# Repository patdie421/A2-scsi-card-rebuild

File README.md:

Apple II SCSI card rebuild

Work in progress, not yet tested.

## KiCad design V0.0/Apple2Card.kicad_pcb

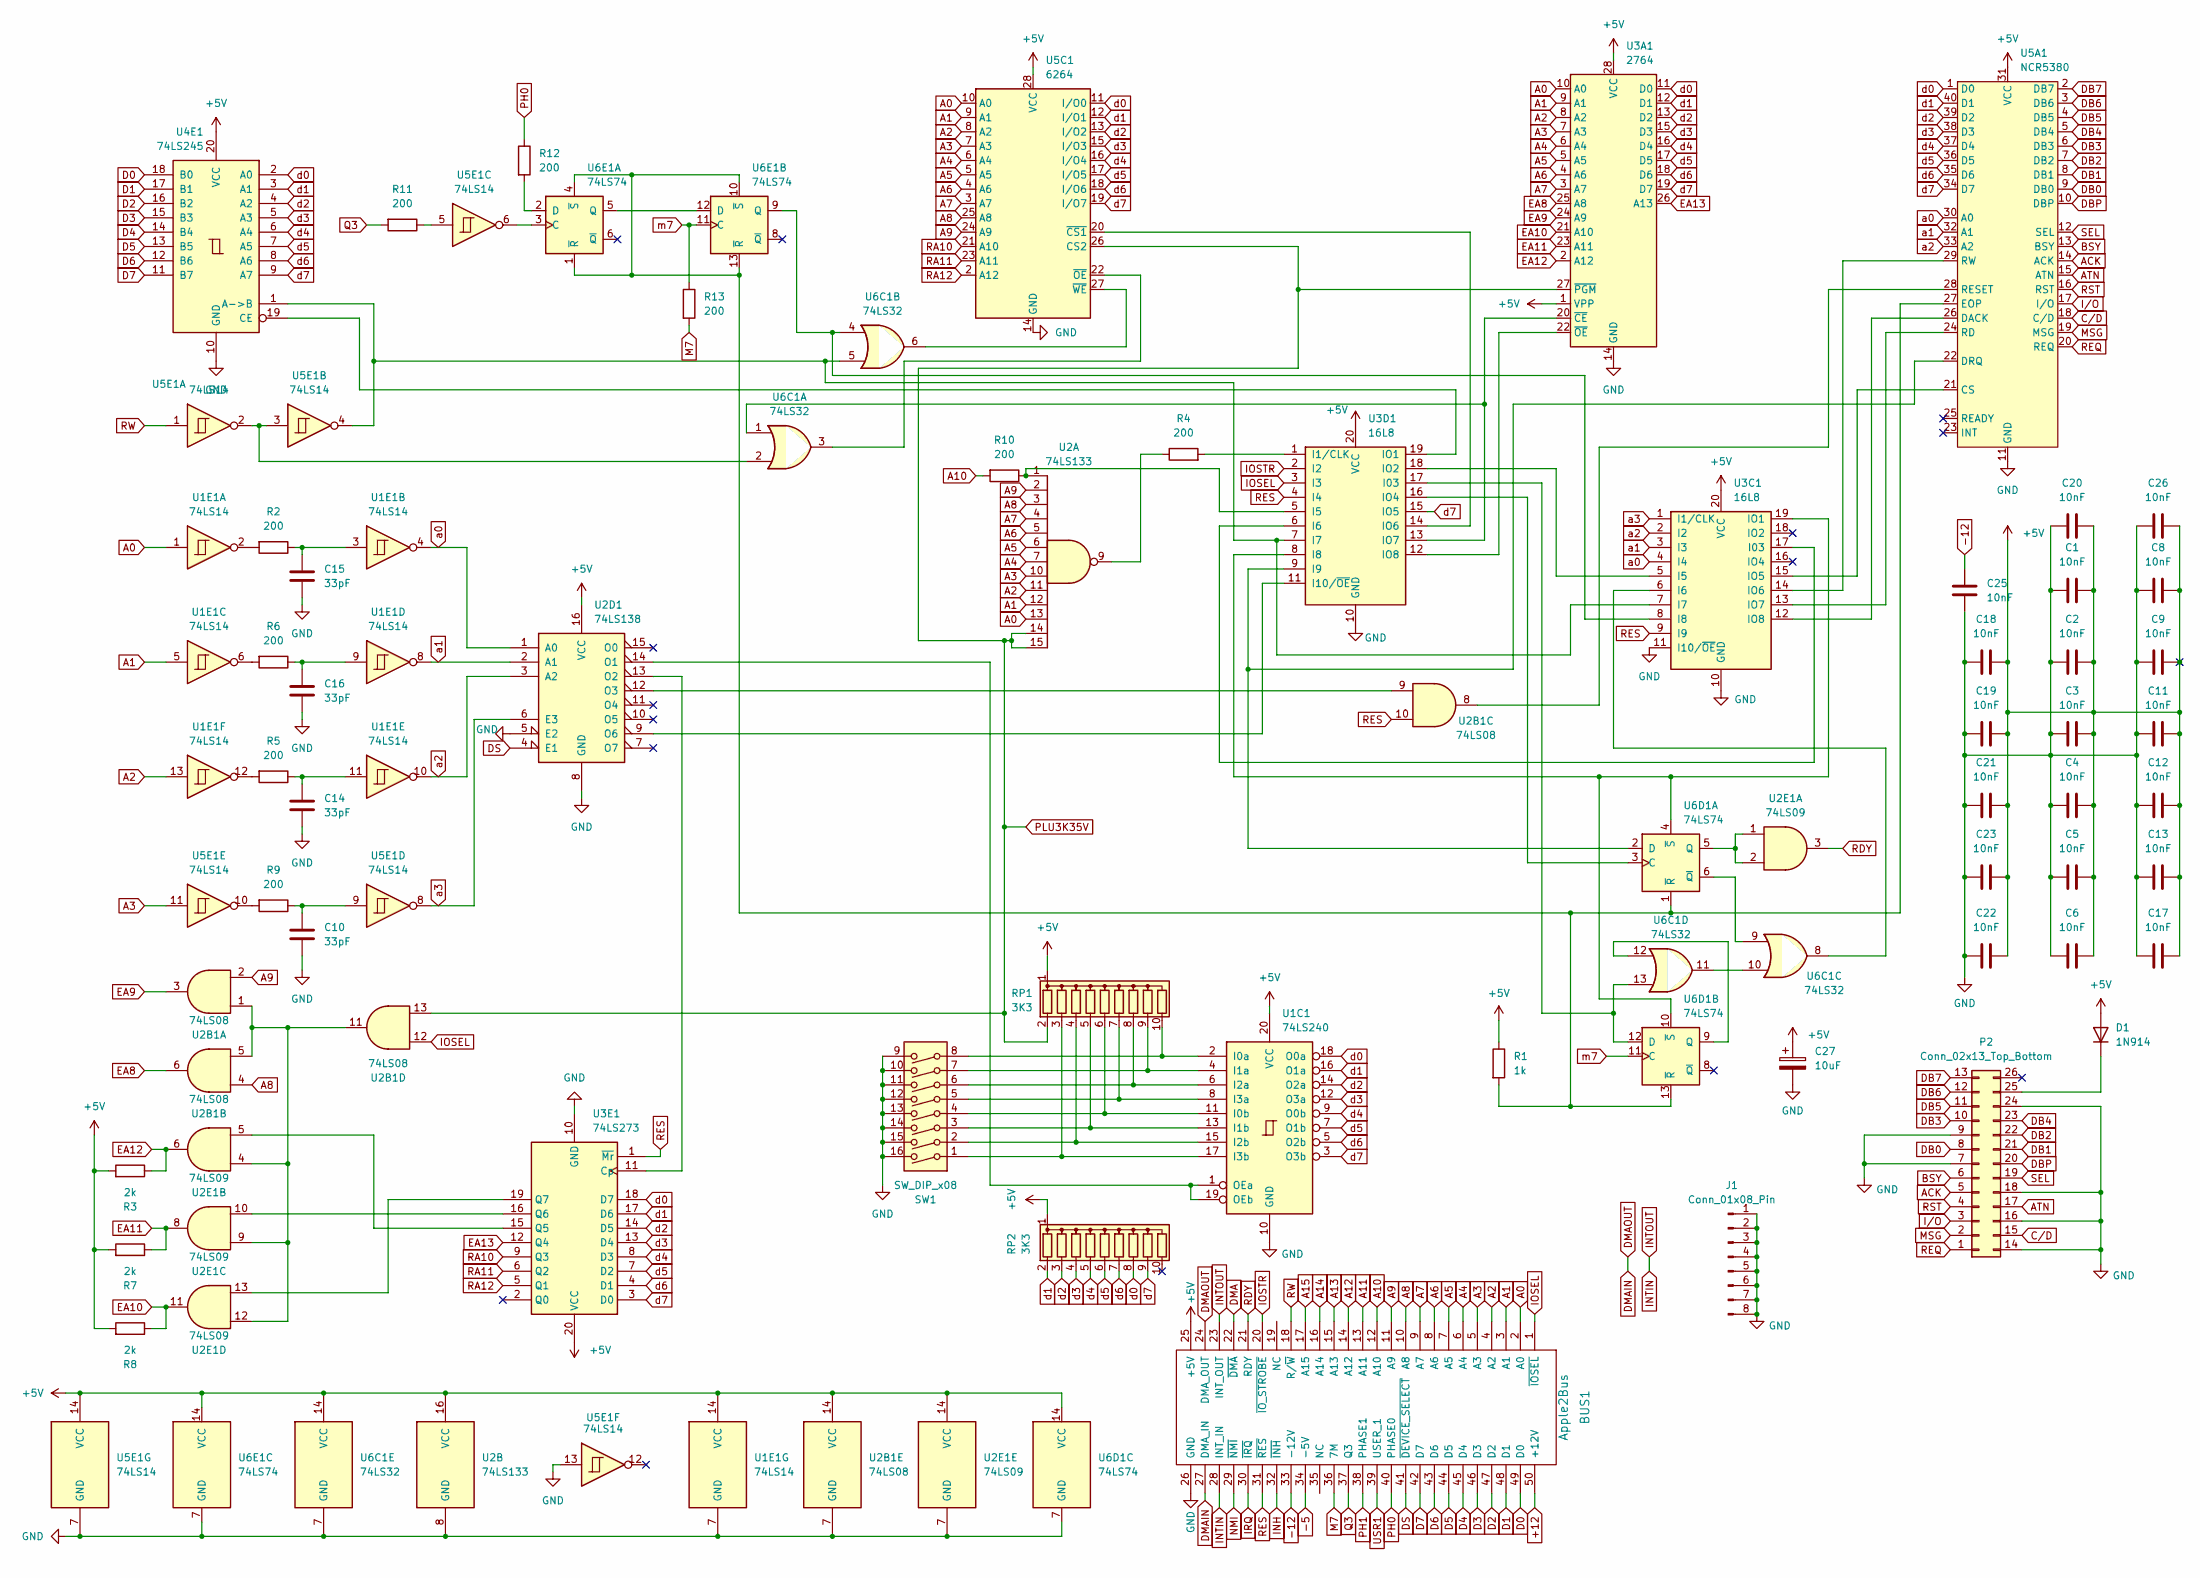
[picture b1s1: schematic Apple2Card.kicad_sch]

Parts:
BUS1: Apple2Bus; Apple2Slot
C1, C2, C3, C4, C5, C6, C8, C9, C11, C12, C13, C17, C18, C19, C20, C21, C22, C23, C25, C26: 10nF; C_Rect_L7.0mm_W2.0mm_P5.00mm
C10, C14, C15, C16: 33pF; C_Rect_L7.0mm_W2.0mm_P5.00mm
C27: 10uF; CP_Radial_D5.0mm_P2.50mm
D1: 1N914; D_DO-35_SOD27_P7.62mm_Horizontal
J1: Conn_01x08_Pin; PinHeader_1x08_P2.54mm_Vertical
P2: Conn_02x13_Top_Bottom; IDC-Header_2x13_P2.54mm_Vertical
R1: 1k; R_Axial_DIN0309_L9.0mm_D3.2mm_P12.70mm_Horizontal
R2, R4, R5, R6, R9, R10, R11, R12, R13: 200; R_Axial_DIN0309_L9.0mm_D3.2mm_P12.70mm_Horizontal
R3, R7, R8: 2k; R_Axial_DIN0309_L9.0mm_D3.2mm_P12.70mm_Horizontal
RP1, RP2: 3K3; R_Array_SIP10
SW1: SW_DIP_x08; CERDIP-16_W7.62mm_SideBrazed
U1C1: 74LS240; DIP-20_W7.62mm
U1E1, U5E1: 74LS14; DIP-14_W7.62mm
U2: 74LS133; DIP-16_W7.62mm
U2B1: 74LS08; DIP-14_W7.62mm
U2D1: 74LS138; DIP-16_W7.62mm
U2E1: 74LS09; DIP-14_W7.62mm
U3A1: 2764; DIP-28_W15.24mm
U3C1, U3D1: 16L8; DIP-20_W7.62mm
U3E1: 74LS273; DIP-20_W7.62mm
U4E1: 74LS245; DIP-20_W7.62mm
U5A1: NCR5380; DIP-40_W15.24mm
U5C1: 6264; DIP-28_W15.24mm
U6C1: 74LS32; DIP-14_W7.62mm
U6D1, U6E1: 74LS74; DIP-14_W7.62mm

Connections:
+5V: BUS1.25 (+5V), C1.1, C2.1, C3.1, C4.1, C5.1, C6.1, C8.1, C9.1, C11.1, C12.1, C13.1, C17.1, C18.1, C19.1, C20.1, C21.1, C22.1, C23.1, C26.1, C27.1, D1.2 (A), R1.1, R3.2, R7.2, R8.2, RP1.1 (common), RP2.1 (common), U1C1.20 (VCC), U1E1.14 (VCC), U2.16 (VCC), U2B1.14 (VCC), U2D1.16 (VCC), U2E1.14 (VCC), U3A1.1 (VPP), U3A1.28 (VCC), U3C1.20 (VCC), U3D1.20 (VCC), U3E1.20 (VCC), U4E1.20 (VCC), U5A1.31 (VCC), U5C1.28 (VCC), U5E1.14 (VCC), U6C1.14 (VCC), U6D1.14 (VCC), U6E1.14 (VCC)
+12: BUS1.50 (+12V)
-5: BUS1.34 (-5V)
-12: BUS1.33 (-12V), C25.2
A0: BUS1.2 (A0), U1E1.1, U2.13, U3A1.10 (A0), U5C1.10 (A0)
A1: BUS1.3 (A1), U1E1.5, U2.12, U3A1.9 (A1), U5C1.9 (A1)
A2: BUS1.4 (A2), U1E1.13, U2.11, U3A1.8 (A2), U5C1.8 (A2)
A3: BUS1.5 (A3), U2.10, U3A1.7 (A3), U5C1.7 (A3), U5E1.11
A4: BUS1.6 (A4), U2.7, U3A1.6 (A4), U5C1.6 (A4)
A5: BUS1.7 (A5), U2.6, U3A1.5 (A5), U5C1.5 (A5)
A6: BUS1.8 (A6), U2.5, U3A1.4 (A6), U5C1.4 (A6)
A7: BUS1.9 (A7), U2.4, U3A1.3 (A7), U5C1.3 (A7)
A8: BUS1.10 (A8), U2.3, U2B1.4, U5C1.25 (A8)
A9: BUS1.11 (A9), U2.2, U2B1.2, U5C1.24 (A9)
A10: BUS1.12 (A10), R10.2
A11: BUS1.13 (A11)
A12: BUS1.14 (A12)
A13: BUS1.15 (A13)
A14: BUS1.16 (A14)
A15: BUS1.17 (A15)
ACK: P2.5, U5A1.14 (ACK)
ATN: P2.17, U5A1.15 (ATN)
BSY: P2.6, U5A1.13 (BSY)
C/D: P2.15, U5A1.18 (C/D)
D0: BUS1.49 (D0), U4E1.18 (B0)
D1: BUS1.48 (D1), U4E1.17 (B1)
D2: BUS1.47 (D2), U4E1.16 (B2)
D3: BUS1.46 (D3), U4E1.15 (B3)
D4: BUS1.45 (D4), U4E1.14 (B4)
D5: BUS1.44 (D5), U4E1.13 (B5)
D6: BUS1.43 (D6), U4E1.12 (B6)
D7: BUS1.42 (D7), U4E1.11 (B7)
DB0: P2.8, U5A1.9 (DB0)
DB1: P2.21, U5A1.8 (DB1)
DB2: P2.22, U5A1.7 (DB2)
DB3: P2.10, U5A1.6 (DB3)
DB4: P2.23, U5A1.5 (DB4)
DB5: P2.11, U5A1.4 (DB5)
DB6: P2.12, U5A1.3 (DB6)
DB7: P2.13, U5A1.2 (DB7)
DBP: P2.20, U5A1.10 (DBP)
DMA: BUS1.22 (~DMA)
DMAIN: BUS1.24 (DMA_OUT), BUS1.27 (DMA_IN)
DS: BUS1.41 (~DEVICE_SELECT), U2D1.4 (E1)
EA8: U2B1.6, U3A1.25 (A8)
EA9: U2B1.3, U3A1.24 (A9)
EA10: R8.1, U2E1.11, U3A1.21 (A10)
EA11: R7.1, U2E1.8, U3A1.23 (A11)
EA12: R3.1, U2E1.6, U3A1.2 (A12)
EA13: U3A1.26 (A13), U3E1.12 (Q4)
GND: BUS1.26 (GND), C1.2, C2.2, C3.2, C4.2, C5.2, C6.2, C8.2, C9.2, C10.2, C11.2, C12.2, C13.2, C14.2, C15.2, C16.2, C17.2, C18.2, C19.2, C20.2, C21.2, C22.2, C23.2, C25.1, C26.2, C27.2, J1.1, J1.2, J1.3, J1.4, J1.5, J1.6, J1.7, J1.8, P2.7, P2.9, P2.14, P2.16, P2.18, P2.24, SW1.9, SW1.10, SW1.11, SW1.12, SW1.13, SW1.14, SW1.15, SW1.16, U1C1.10 (GND), U1E1.7 (GND), U2.8 (GND), U2B1.7 (GND), U2D1.5 (E2), U2D1.8 (GND), U2E1.7 (GND), U3A1.14 (GND), U3C1.10 (GND), U3C1.11 (I10/~OE), U3D1.10 (GND), U3E1.10 (GND), U4E1.10 (GND), U5A1.11 (GND), U5C1.14 (GND), U5E1.7 (GND), U5E1.13, U6C1.7 (GND), U6D1.7 (GND), U6E1.7 (GND)
INH: BUS1.32 (~INH)
INTIN: BUS1.23 (INT_OUT), BUS1.28 (INT_IN)
IOSEL: BUS1.1 (~IOSEL), U2B1.12, U3D1.3 (I3)
IOSTR: BUS1.20 (~IO_STROBE), U3D1.2 (I2)
IRQ: BUS1.30 (~IRQ)
I/O: P2.3, U5A1.17 (I/O)
M7: BUS1.36 (7M), R13.2
MSG: P2.2, U5A1.19 (MSG)
NMI: BUS1.29 (~NMI)
unnamed: C10.1, R9.1, U5E1.9
unnamed: C14.1, R5.1, U1E1.11
unnamed: C15.1, R2.1, U1E1.3
unnamed: C16.1, R6.1, U1E1.9
unnamed: D1.1 (K), P2.25
unnamed: R2.2, U1E1.2
unnamed: R4.1, U2.9
unnamed: R5.2, U1E1.12
unnamed: R6.2, U1E1.6
unnamed: R9.2, U5E1.10
unnamed: R11.1, U5E1.5
unnamed: RP1.3 (R2), SW1.1, U1C1.17 (I3b)
unnamed: RP1.4 (R3), SW1.2, U1C1.15 (I2b)
unnamed: RP1.5 (R4), SW1.3, U1C1.13 (I1b)
unnamed: RP1.6 (R5), SW1.4, U1C1.11 (I0b)
unnamed: RP1.7 (R6), SW1.5, U1C1.8 (I3a)
unnamed: RP1.8 (R7), SW1.6, U1C1.6 (I2a)
unnamed: RP1.9 (R8), SW1.7, U1C1.4 (I1a)
unnamed: RP1.10 (R9), SW1.8, U1C1.2 (I0a)
unnamed: U1C1.1 (OEa), U1C1.19 (OEb), U2D1.14 (O1)
unnamed: U2B1.1, U2B1.5, U2B1.11, U2E1.4, U2E1.9, U2E1.12
unnamed: U2D1.13 (O2), U3E1.11 (Cp)
unnamed: U2B1.9, U2D1.12 (O3)
unnamed: U2D1.9 (O6), U3D1.11 (I10/~OE)
unnamed: U3A1.20 (~CE), U3D1.13 (IO7), U6C1.1
unnamed: U3A1.22 (~OE), U3D1.12 (IO8)
unnamed: U3C1.17 (I03), U3D1.6 (I6)
unnamed: U3C1.5 (I5), U3D1.18 (IO2)
unnamed: U3C1.6 (I6), U6C1.8
unnamed: U3C1.7 (I7), U3D1.7 (I7), U4E1.1 (A->B), U5E1.4, U6C1.5
unnamed: U3C1.8 (I8), U6C1.4, U6E1.9 (Q)
unnamed: U3C1.19 (IO1), U3D1.8 (I8), U6D1.4 (~S), U6D1.10 (~S)
unnamed: U3C1.15 (IO5), U5A1.21 (CS)
unnamed: U3C1.14 (IO6), U5A1.29 (RW)
unnamed: U3C1.13 (IO7), U5A1.24 (RD)
unnamed: U3C1.12 (IO8), U5A1.26 (DACK)
unnamed: R4.2, U3D1.1 (I1/CLK)
unnamed: U3D1.17 (I03), U6C1.13, U6D1.12 (D)
unnamed: R10.1, U2.1, U3D1.5 (I5)
unnamed: U3D1.9 (I9), U5A1.22 (DRQ), U6D1.2 (D)
unnamed: U3D1.19 (IO1), U4E1.19 (CE)
unnamed: U3D1.16 (IO4), U6D1.3 (C)
unnamed: U3D1.14 (IO6), U5C1.20 (~CS1)
unnamed: U2E1.5, U3E1.15 (Q5)
unnamed: U2E1.10, U3E1.16 (Q6)
unnamed: U2E1.13, U3E1.19 (Q7)
unnamed: R1.2, U5A1.27 (EOP), U6D1.1 (~R), U6D1.13 (~R), U6E1.1 (~R), U6E1.4 (~S), U6E1.10 (~S), U6E1.13 (~R)
unnamed: U2B1.8, U5A1.28 (RESET)
unnamed: U5C1.22 (~OE), U6C1.3
unnamed: U5C1.27 (~WE), U6C1.6
unnamed: U5E1.2, U5E1.3, U6C1.2
unnamed: U6C1.10, U6C1.11
unnamed: U2E1.1, U2E1.2, U6D1.5 (Q)
unnamed: U6C1.9, U6D1.6 (~Q)
unnamed: U6C1.12, U6D1.9 (Q)
unnamed: U5E1.6, U6E1.3 (C)
unnamed: R12.2, U6E1.2 (D)
unnamed: U6E1.5 (Q), U6E1.12 (D)
PH0: BUS1.40 (PHASE0), R12.1
PH1: BUS1.38 (PHASE1)
PLU3K35V: RP1.2 (R1), U2.14, U2.15, U2B1.13, U3A1.27 (~PGM), U5C1.26 (CS2)
Q3: BUS1.37 (Q3), R11.2
RA10: U3E1.9 (Q3), U5C1.21 (A10)
RA11: U3E1.6 (Q2), U5C1.23 (A11)
RA12: U3E1.5 (Q1), U5C1.2 (A12)
RDY: BUS1.21 (RDY), U2E1.3
REQ: P2.1, U5A1.20 (REQ)
RES: BUS1.31 (~RES), U2B1.10, U3C1.9 (I9), U3D1.4 (I4), U3E1.1 (~Mr)
RST: P2.4, U5A1.16 (RST)
RW: BUS1.18 (R/~W), U5E1.1
SEL: P2.19, U5A1.12 (SEL)
USR1: BUS1.39 (USER_1)
a0: U1E1.4, U2D1.1 (A0), U3C1.4 (I4), U5A1.30 (A0)
a1: U1E1.8, U2D1.2 (A1), U3C1.3 (I3), U5A1.32 (A1)
a2: U1E1.10, U2D1.3 (A2), U3C1.2 (I2), U5A1.33 (A2)
a3: U2D1.6 (E3), U3C1.1 (I1/CLK), U5E1.8
d0: RP2.8 (R7), U1C1.18 (O0a), U3A1.11 (D0), U3E1.18 (D7), U4E1.2 (A0), U5A1.1 (D0), U5C1.11 (I/O0)
d1: RP2.2 (R1), U1C1.16 (O1a), U3A1.12 (D1), U3E1.17 (D6), U4E1.3 (A1), U5A1.40 (D1), U5C1.12 (I/O1)
d2: RP2.3 (R2), U1C1.14 (O2a), U3A1.13 (D2), U3E1.14 (D5), U4E1.4 (A2), U5A1.39 (D2), U5C1.13 (I/O2)
d3: RP2.4 (R3), U1C1.12 (O3a), U3A1.15 (D3), U3E1.13 (D4), U4E1.5 (A3), U5A1.38 (D3), U5C1.15 (I/O3)
d4: RP2.5 (R4), U1C1.9 (O0b), U3A1.16 (D4), U3E1.8 (D3), U4E1.6 (A4), U5A1.37 (D4), U5C1.16 (I/O4)
d5: RP2.6 (R5), U1C1.7 (O1b), U3A1.17 (D5), U3E1.7 (D2), U4E1.7 (A5), U5A1.36 (D5), U5C1.17 (I/O5)
d6: RP2.7 (R6), U1C1.5 (O2b), U3A1.18 (D6), U3E1.4 (D1), U4E1.8 (A6), U5A1.35 (D6), U5C1.18 (I/O6)
d7: RP2.9 (R8), U1C1.3 (O3b), U3A1.19 (D7), U3D1.15 (IO5), U3E1.3 (D0), U4E1.9 (A7), U5A1.34 (D7), U5C1.19 (I/O7)
m7: R13.1, U6D1.11 (C), U6E1.11 (C)

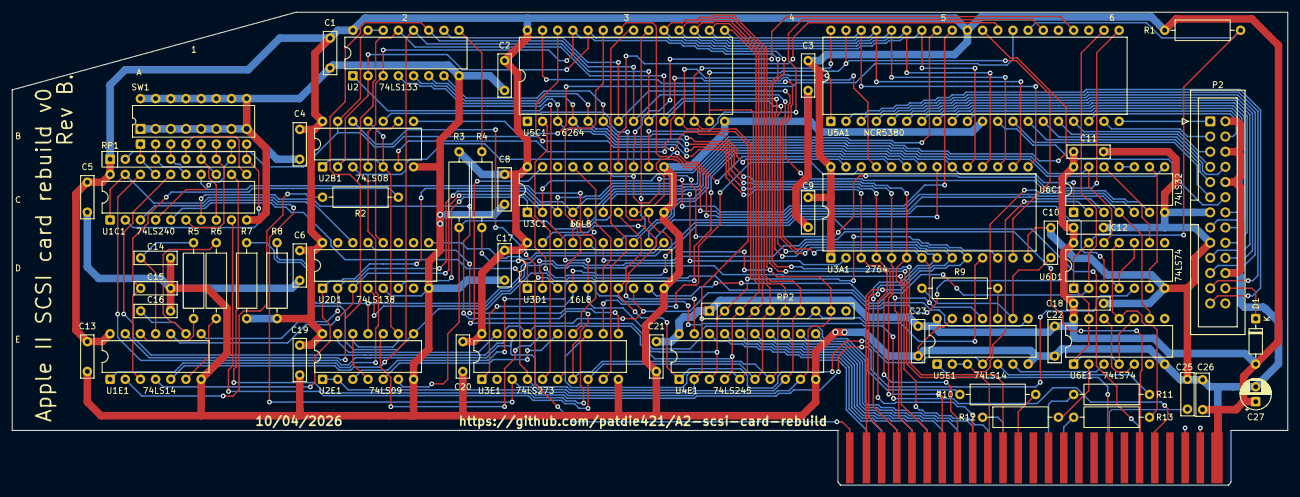
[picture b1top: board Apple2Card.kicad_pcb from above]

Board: 2 copper layers, 213.5 x 79.1 mm, 62 parts (0 on the bottom side), 132 nets.

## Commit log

2026-03-27 init
2026-03-27 add org schema and rom
2026-03-27 schema and png
2026-03-27 Photo
2026-03-28 PAL eqn validation
2026-03-28 update schema
2026-03-28 cleanup
2026-03-28 PAL code
2026-03-29 good kicad file
2026-03-29 pld files added
2026-03-29 directory organisation
2026-03-29 add gerber files
2026-03-29 Update README to reflect Apple II SCSI card
2026-03-29 renaming ...
2026-03-29 Update README to reflect project status
    Added a note indicating that the project is a work in progress and not yet tested.
2026-03-29 update to remove 74LS09
2026-03-30 BS170 to 2N3904
2026-04-12 menage
2026-04-12 correction
2026-04-16 Rename U3C_342-0415-A.pld to U3C_342-0415-A_U3C.pld
2026-04-16 Rename U3C_342-0415-A_U3C.pld to U3C_342-0415-A.pld
